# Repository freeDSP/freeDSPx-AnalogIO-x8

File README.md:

# AnalogIO-x8
Expansionboard with 8 analog balanced inputs and 8 analog balanced outputs for Infinitas and other freeDSPs

BOARD STATUS: Released!

MAIN COORDINATOR: [dspverden](https://github.com/dspverden)

IMPORTANT:

Please take care on which branch you're currently working!

Branches:

master - this branch always holds the latest released revision
develop - this is the develop branch with new features

## License
The plans for the AnalogIO-x8 board are published under a Creative Commons Attribution NonCommercial ShareAlike 4.0 International (CC BY-NC-SA 4.0) license, which allows the unrestricted use and modification of the module for non-commercial purposes. This means that experienced users can make their own version of the board, extending it and improving it, as long as they credit freeDSP and auverdion and release their designs under the same license.

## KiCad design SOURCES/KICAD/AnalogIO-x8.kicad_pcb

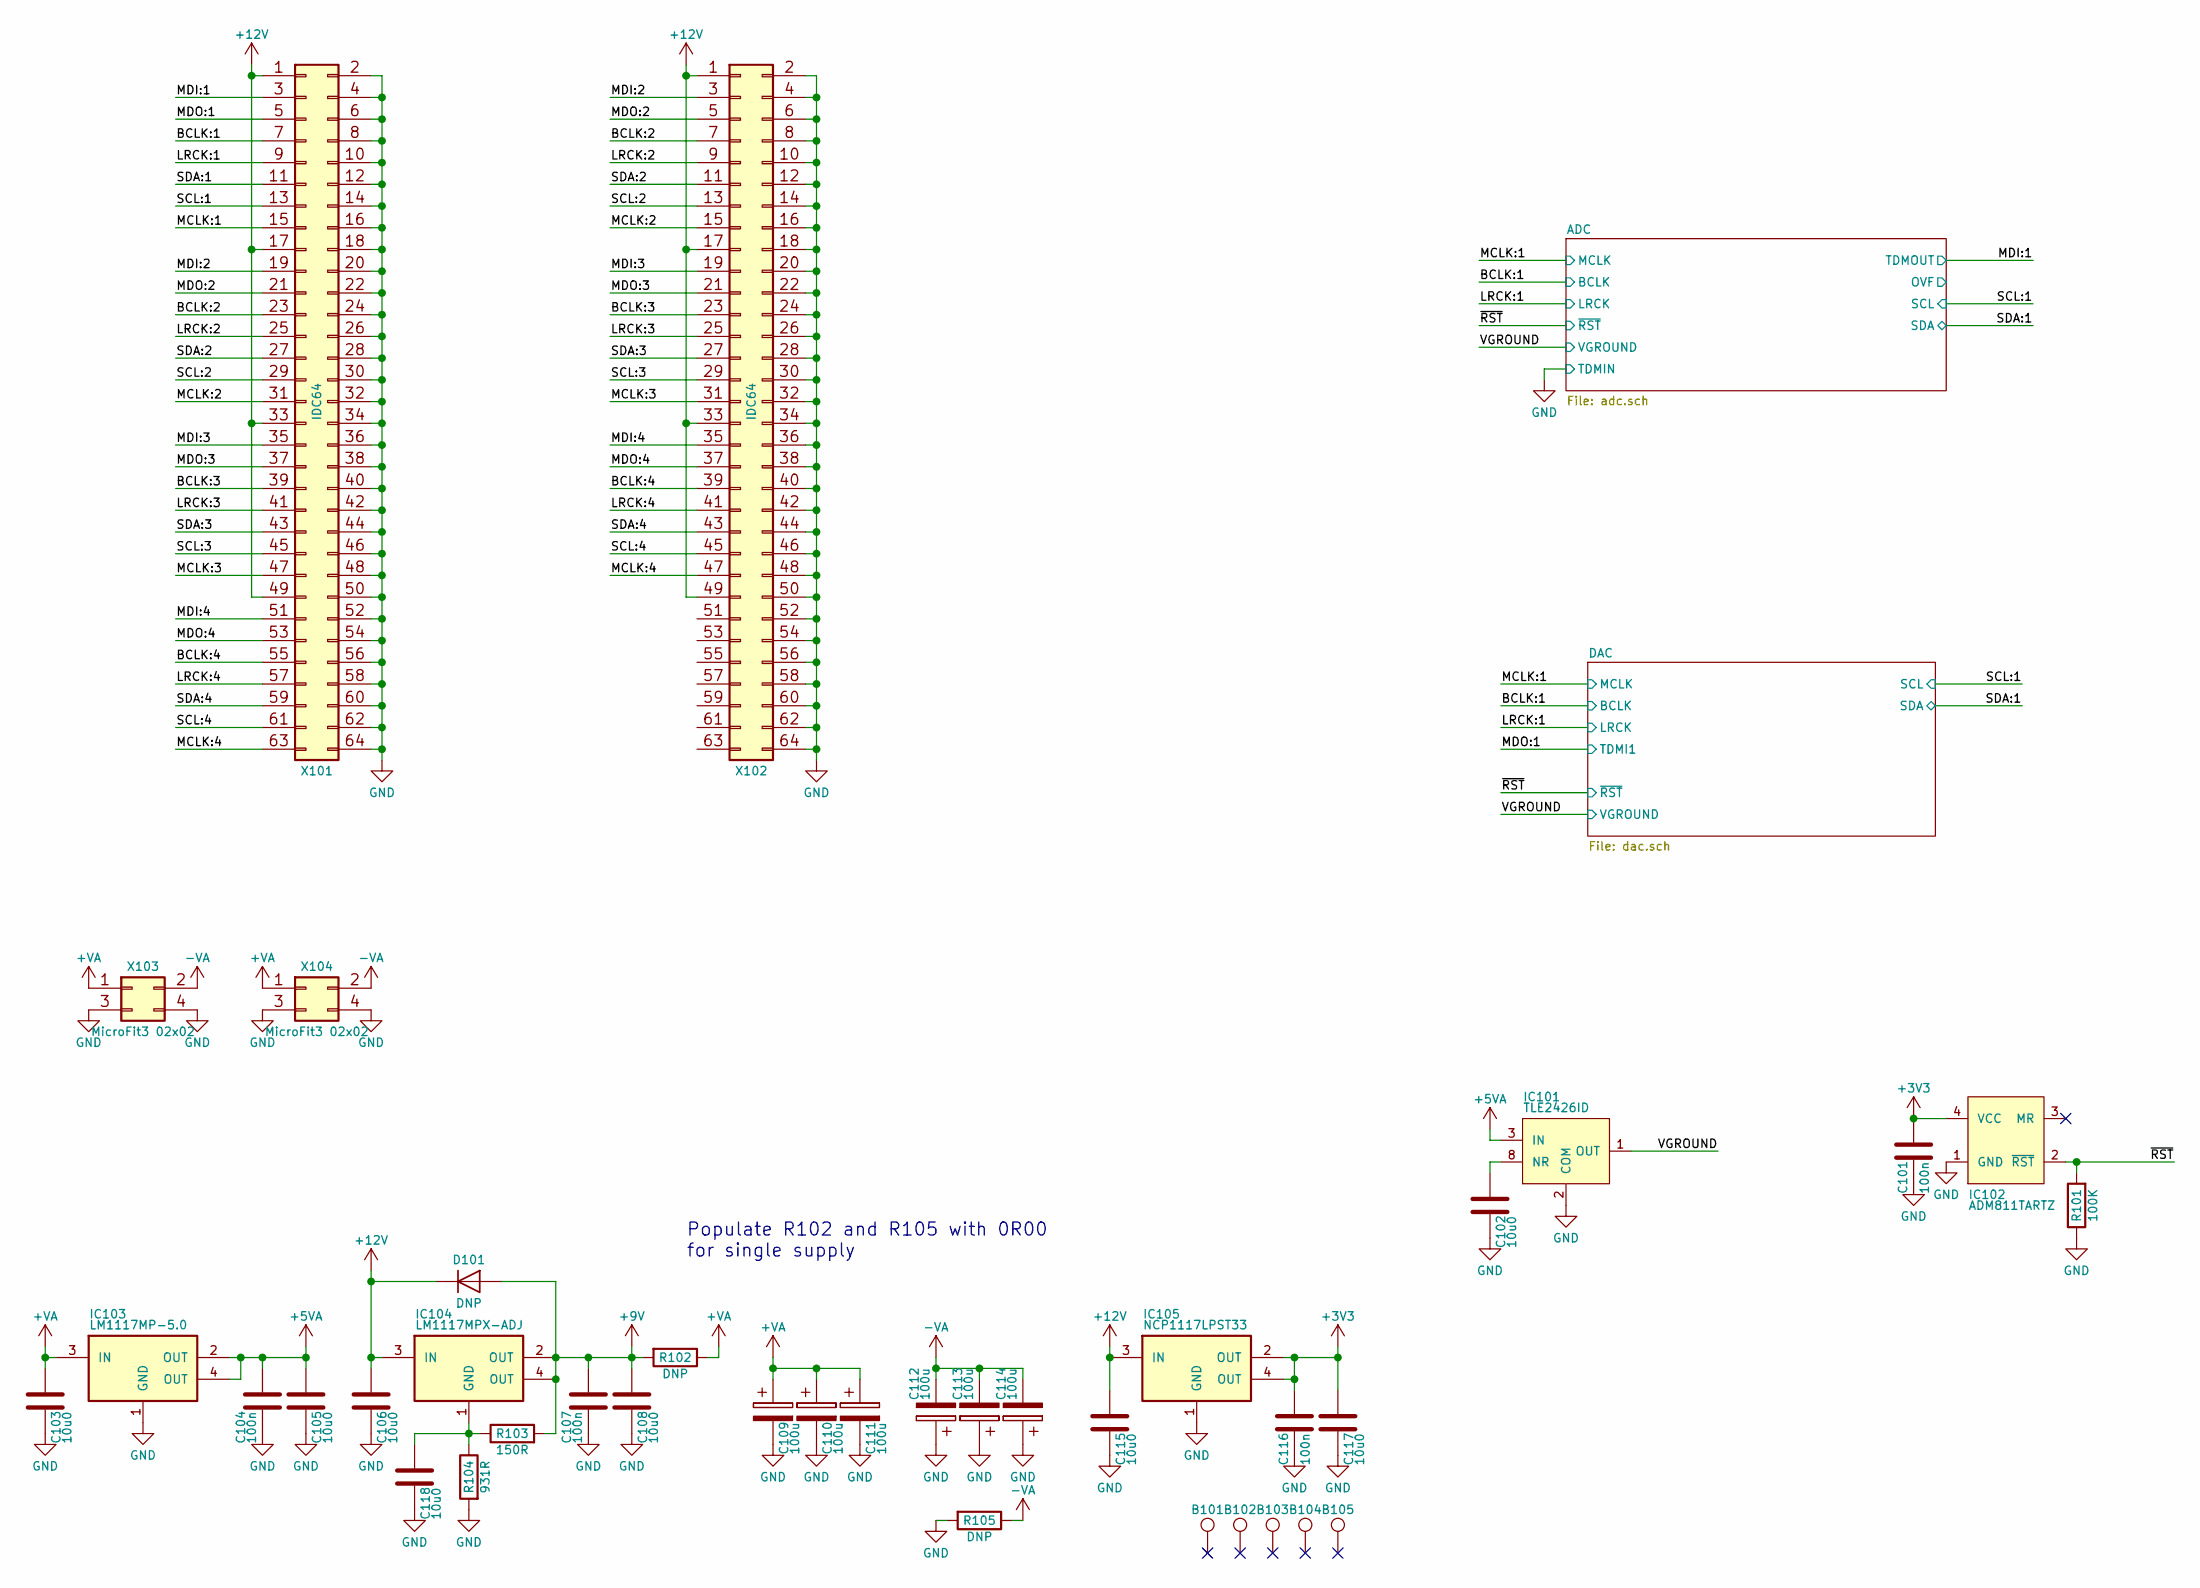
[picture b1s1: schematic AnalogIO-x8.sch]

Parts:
B101, B102, B103, B104, B105: TEST_1P; MountingHole_3.2mm_M3_DIN965_Pad
C101, C104, C107, C116: CAP_100n_50V_X7R_0805; C0805-X7R; digikey 399-1170-1-ND
C102, C103, C105, C106, C108, C115, C117, C118: CAP_10u0_25V_X5R_0805; C0805-X7R; digikey 490-10748-1-ND
C109, C110, C111, C112, C113, C114: CAP_100u_20%_25V_ALUM_RADIAL; C_Radial_D5_L11_P2; digikey 399-6102-ND
D101: DNP; MELF_Standard
IC101: IC_TLE2426ID; SOIC-8_3.9x4.9mm_Pitch1.27mm; digikey 296-1345-1-ND
IC102: IC_ADM811TARTZ; SOT-143; digikey ADM811TARTZ-REELCT-ND
IC103: IC_LM1117MP-5.0; SOT-223; digikey LM1117MP-5.0/NOPBCT-ND
IC104: IC_LM1117MPX-ADJ; SOT-223; digikey LM1117MPX-ADJ/NOPBCT-ND
IC105: IC_NCP1117LPST33; SOT-223; digikey NCP1117LPST33T3GOSCT-ND
R101: RES_100K_1%_0.125W_Thick_0805; C0805-RES; digikey 311-100KCRCT-ND
R102, R105: DNP; Resistor_Horizontal_RM7mm
R103: RES_150R_1%_0.25W_Thin_0805; C0805-RES; digikey RNCP0805FTD150RCT-ND
R104: RES_931R_1%_0.125W_Thick_0805; C0805-RES; digikey 311-931CRCT-ND
X101, X102: CON_IDC64; IDC64; digikey ED10532-ND
X103, X104: CON_MicroFit3_02x02; Microfit3_43045-0428; digikey WM10670-ND

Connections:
+3V3: C101.2, C116.2, C117.1, IC102.4 (VCC), IC105.2 (OUT), IC105.4 (OUT); also elsewhere on the board
+5VA: C104.2, C105.1, IC101.3 (IN), IC103.2 (OUT), IC103.4 (OUT); also elsewhere on the board
+9V: C107.2, C108.1, D101.2 (A), IC104.2 (OUT), IC104.4 (OUT), R102.2, R103.2
+12V: C106.1, C115.1, D101.1 (K), IC104.3 (IN), IC105.3 (IN), X101.1, X101.17, X101.33, X101.49, X102.1, X102.17, X102.33, X102.49
+VA: C103.1, C109.1, C110.1, C111.1, IC103.3 (IN), R102.1, X103.1, X104.1; also elsewhere on the board
-VA: C112.2, C113.2, C114.2, R105.1, X103.2, X104.2; also elsewhere on the board
/BCLK:1: X101.7; also elsewhere on the board
/BCLK:2: X101.23, X102.7
/BCLK:3: X101.39, X102.23
/BCLK:4: X101.55, X102.39
/LRCK:1: X101.9; also elsewhere on the board
/LRCK:2: X101.25, X102.9
/LRCK:3: X101.41, X102.25
/LRCK:4: X101.57, X102.41
/MCLK:1: X101.15; also elsewhere on the board
/MCLK:2: X101.31, X102.15
/MCLK:3: X101.47, X102.31
/MCLK:4: X101.63, X102.47
/MDI:1: X101.3; also elsewhere on the board
/MDI:2: X101.19, X102.3
/MDI:3: X101.35, X102.19
/MDI:4: X101.51, X102.35
/MDO:1: X101.5; also elsewhere on the board
/MDO:2: X101.21, X102.5
/MDO:3: X101.37, X102.21
/MDO:4: X101.53, X102.37
/SCL:1: X101.13; also elsewhere on the board
/SCL:2: X101.29, X102.13
/SCL:3: X101.45, X102.29
/SCL:4: X101.61, X102.45
/SDA:1: X101.11; also elsewhere on the board
/SDA:2: X101.27, X102.11
/SDA:3: X101.43, X102.27
/SDA:4: X101.59, X102.43
/VGROUND: IC101.1 (OUT); also elsewhere on the board
/~RST: IC102.2 (~RST), R101.2; also elsewhere on the board
GND: C101.1, C102.2, C103.2, C104.1, C105.2, C106.2, C107.1, C108.2, C109.2, C110.2, C111.2, C112.1, C113.1, C114.1, C115.2, C116.1, C117.2, C118.2, IC101.2 (COM), IC102.1 (GND), IC103.1 (GND), IC105.1 (GND), R101.1, R104.2, R105.2, X101.2, X101.4, X101.6, X101.8, X101.10, X101.12, X101.14, X101.16, X101.18, X101.20, X101.22, X101.24, X101.26, X101.28, X101.30, X101.32, X101.34, X101.36, X101.38, X101.40, X101.42, X101.44, X101.46, X101.48, X101.50, X101.52, X101.54, X101.56, X101.58, X101.60, X101.62, X101.64, X102.2, X102.4, X102.6, X102.8, X102.10, X102.12, X102.14, X102.16, X102.18, X102.20, X102.22, X102.24, X102.26, X102.28, X102.30, X102.32, X102.34, X102.36, X102.38, X102.40, X102.42, X102.44, X102.46, X102.48, X102.50, X102.52, X102.54, X102.56, X102.58, X102.60, X102.62, X102.64, X103.3, X103.4, X104.3, X104.4; also elsewhere on the board
unnamed: C102.1, IC101.8 (NR)
unnamed: C118.1, IC104.1 (GND), R103.1, R104.1

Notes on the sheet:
Populate R102 and R105 with 0R00 for single supply

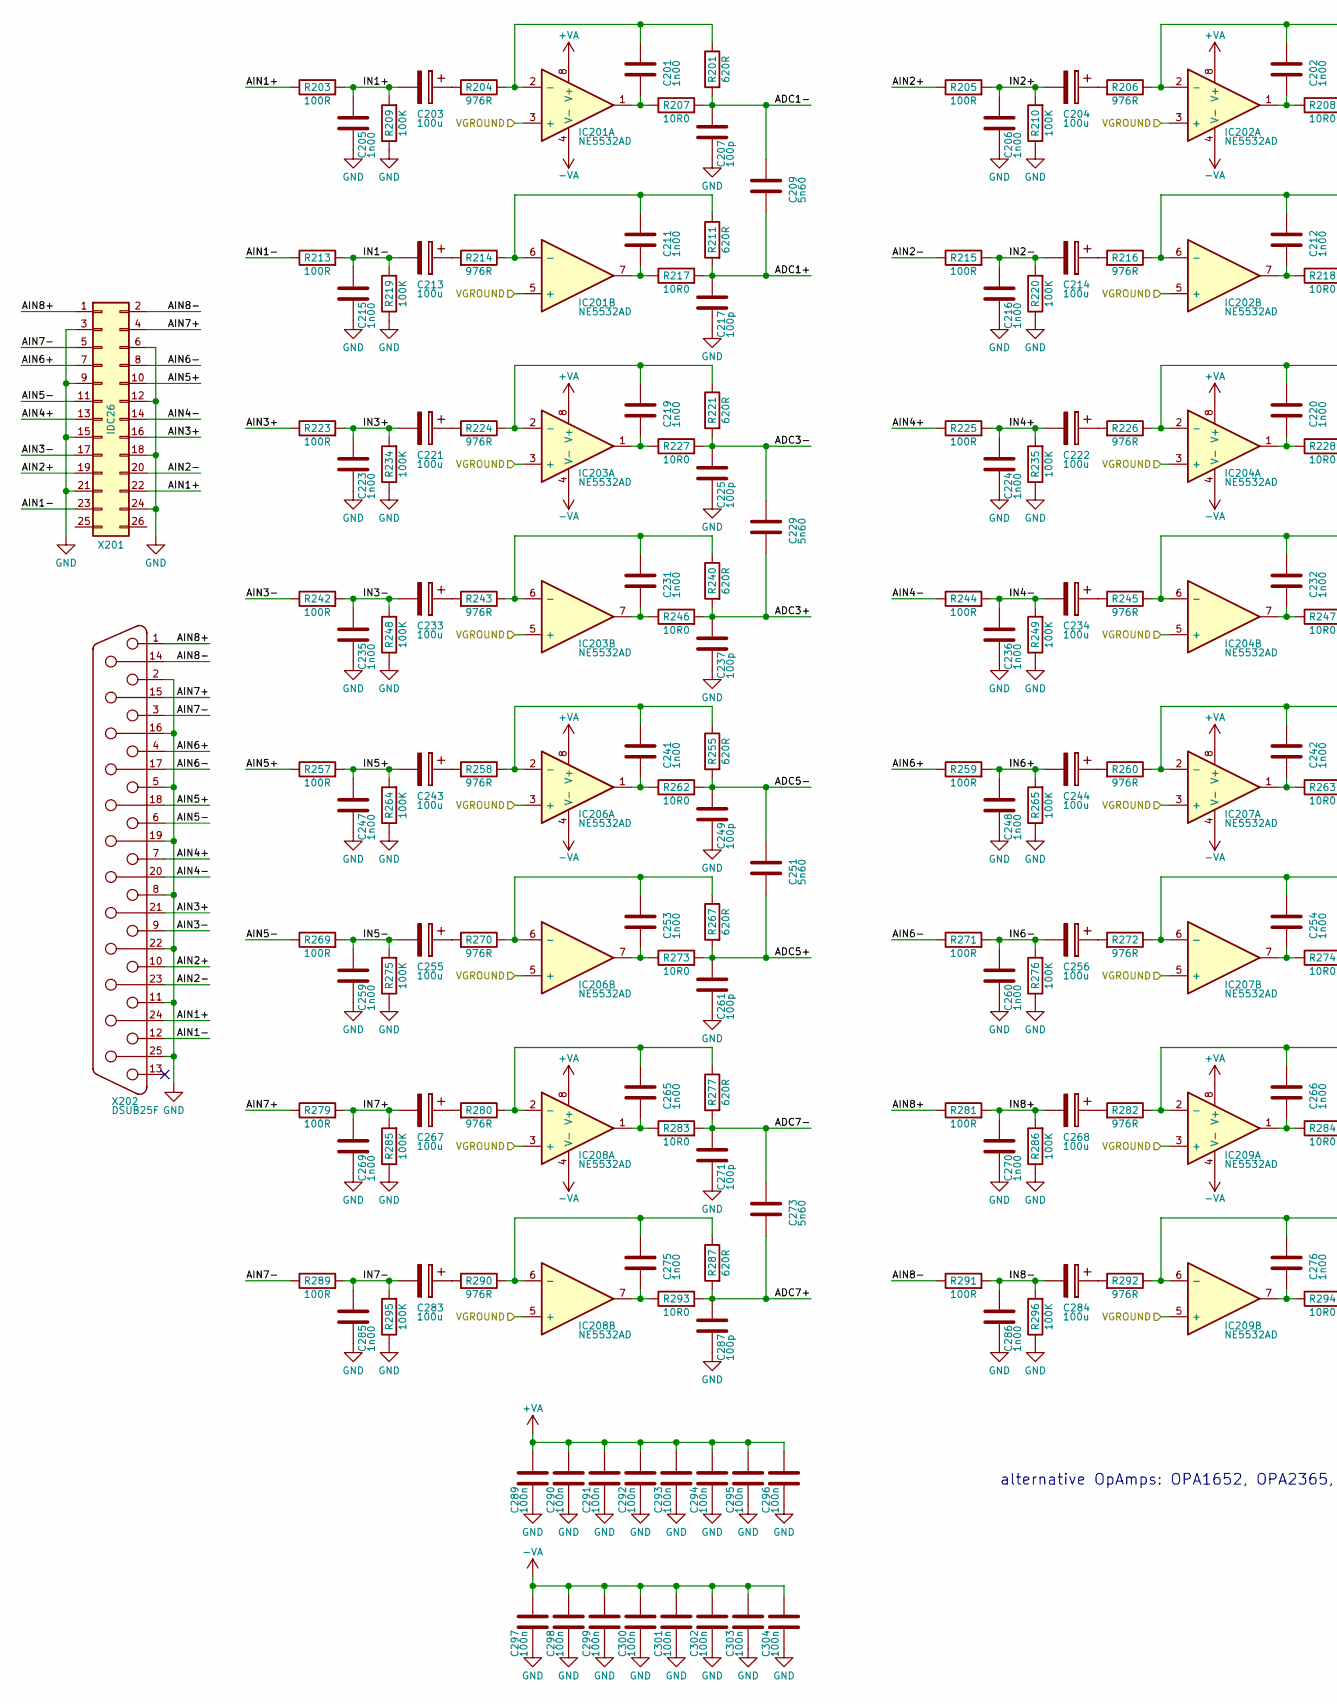
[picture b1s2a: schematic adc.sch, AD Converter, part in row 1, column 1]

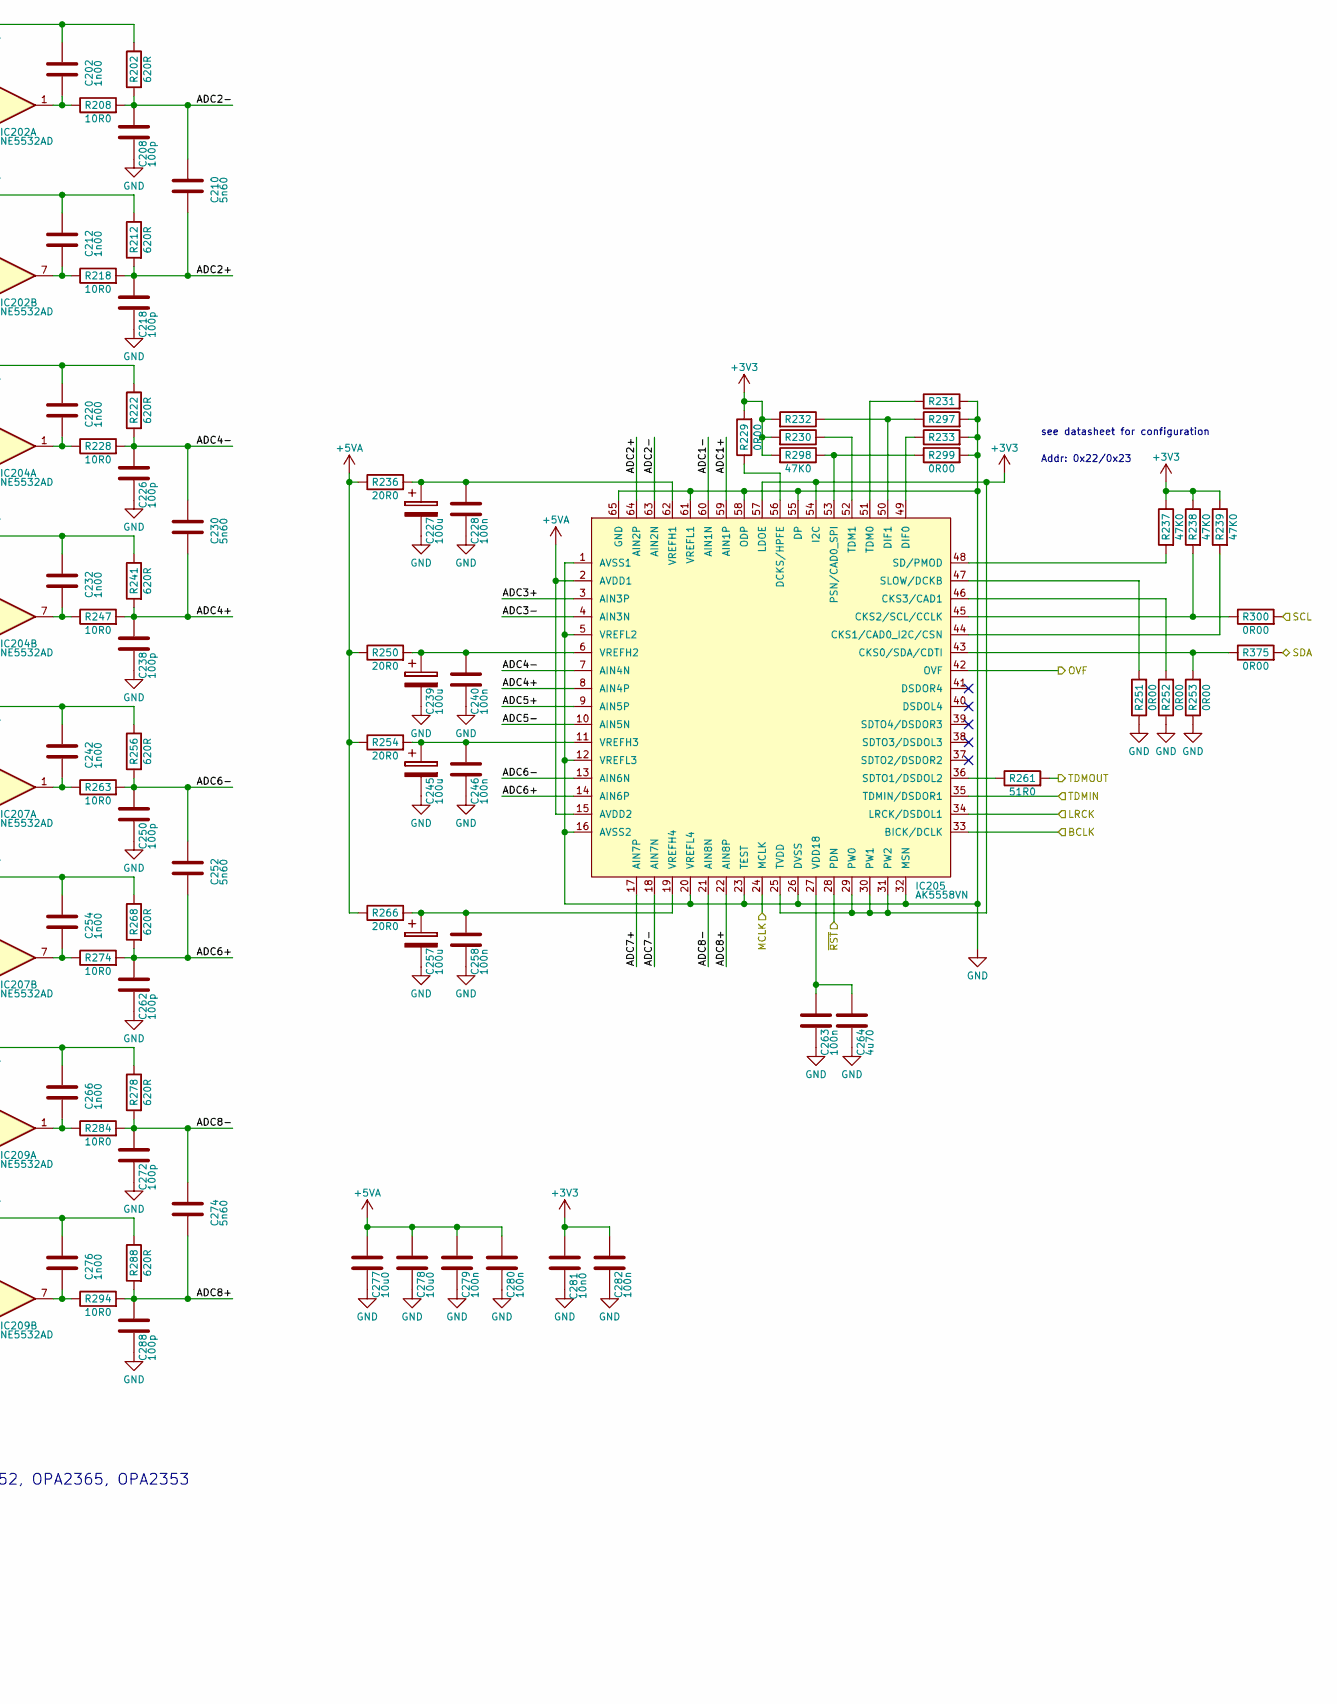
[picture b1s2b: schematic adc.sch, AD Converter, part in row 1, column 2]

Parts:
C201, C202, C211, C212, C219, C220, C231, C232, C241, C242, C253, C254, C265, C266, C275, C276: CAP_1n00_5%_50V_PPS_0805; C0805-X7R; digikey PCF1328CT-ND
C203, C204, C213, C214, C221, C222, C227, C233, C234, C239, C243, C244, C245, C255, C256, C257, C267, C268, C283, C284: CAP_100u_20%_25V_ALUM_RADIAL; C_Radial_D5_L11_P2; digikey 399-6102-ND
C205, C206, C215, C216, C223, C224, C235, C236, C247, C248, C259, C260, C269, C270, C285, C286: CAP_1n00_50V_X7R_0805; C0805-X7R; digikey 399-1147-1-ND
C207, C208, C217, C218, C225, C226, C237, C238, C249, C250, C261, C262, C271, C272, C287, C288: CAP_100p_50V_C0G/NP0_0805; C0805-X7R; digikey 399-1122-1-ND
C209, C210, C229, C230, C251, C252, C273, C274: CAP_5n60_5%_16V_PPS_0805; C0805-X7R; digikey PCF1193CT-ND
C228, C240, C246, C258, C263, C279, C280, C282, C289, C290, C291, C292, C293, C294, C295, C296, C297, C298, C299, C300, C301, C302, C303, C304: CAP_100n_50V_X7R_0805; C0805-X7R; digikey 399-1170-1-ND
C264: CAP_4u70_25V_X5R_0805; C0805-X7R; digikey 490-5422-1-ND
C277, C278: CAP_10u0_25V_X5R_0805; C0805-X7R; digikey 490-10748-1-ND
C281: CAP_10n0_50V_X7R_0805; C0805-X7R; digikey 311-1136-1-ND
IC201, IC202, IC203, IC204, IC206, IC207, IC208, IC209: IC_NE5532AD_SOIC8; SOIC8_3.9x4.9mm_Pitch1.27mm; digikey NE5532AD8R2GOSCT-ND
IC205: IC_AK5558VN; QFN64_9x9mm_Pitch0.5mm_EP_Handsoldering; digikey 974-1128-1-ND
R201, R202, R211, R212, R221, R222, R240, R241, R255, R256, R267, R268, R277, R278, R287, R288: RES_620R_0.5%_0.1W_Thin_0805; C0805-RES; digikey RR12P620DCT-ND
R203, R205, R213, R215, R223, R225, R242, R244, R257, R259, R269, R271, R279, R281, R289, R291: RES_100R_1%_0.25W_Thin_0805; C0805-RES; digikey RNCP0805FTD100RCT-ND
R204, R206, R214, R216, R224, R226, R243, R245, R258, R260, R270, R272, R280, R282, R290, R292: RES_976R_0.5%_0.1W_Thin_0805; C0805-RES; digikey 408-1761-1-ND
R207, R208, R217, R218, R227, R228, R246, R247, R262, R263, R273, R274, R283, R284, R293, R294: RES_10R0_1%_0.25W_Thin_0805; C0805-RES; digikey RNCP0805FTD10R0CT-ND
R209, R210, R219, R220, R234, R235, R248, R249, R264, R265, R275, R276, R285, R286, R295, R296: RES_100K_1%_0.125W_Thick_0805; C0805-RES; digikey 311-100KCRCT-ND
R229, R231, R233, R251, R252, R253, R297, R299, R300, R375: RES_0R00_1%_0.125W_Thick_0805; C0805-RES; digikey 311-0.0ARCT-ND
R230, R232, R237, R238, R239, R298: RES_47K0_1%_0.125W_Thick_0805; C0805-RES; digikey 311-47.0KCRCT-ND
R236, R250, R254, R266: RES_20R0_1%_0.125W_Thick_0805; C0805-RES; digikey 311-20.0CRCT-ND
R261: RES_51R0_1%_0.125W_Thick_0805; C0805-RES; digikey 311-51.0CRCT-ND
X201: CON_IDC26; IDC_Header_Straight_26pins; digikey 377-2269-ND
X202: CON_DSUB25F; DSUB25FC; digikey AE10937-ND

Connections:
+3V3: C281.1, C282.2, IC205.25 (TVDD), IC205.29 (PW0), IC205.30 (PW1), IC205.31 (PW2), IC205.54 (I2C), IC205.57 (LDOE), R229.2, R230.2, R232.2, R237.1, R238.1, R239.1, R298.2; also elsewhere on the board
+5VA: C277.1, C278.1, C279.2, C280.2, IC205.2 (AVDD1), IC205.15 (AVDD2), R236.1, R250.1, R254.1, R266.1; also elsewhere on the board
+VA: C289.2, C290.2, C291.2, C292.2, C293.2, C294.2, C295.2, C296.2, IC201.8 (V+), IC202.8 (V+), IC203.8 (V+), IC204.8 (V+), IC206.8 (V+), IC207.8 (V+), IC208.8 (V+), IC209.8 (V+); also elsewhere on the board
-VA: C297.2, C298.2, C299.2, C300.2, C301.2, C302.2, C303.2, C304.2, IC201.4 (V-), IC202.4 (V-), IC203.4 (V-), IC204.4 (V-), IC206.4 (V-), IC207.4 (V-), IC208.4 (V-), IC209.4 (V-); also elsewhere on the board
/ADC-1/ADC1+: C209.2, C217.2, IC205.59 (AIN1P), R211.2, R217.2
/ADC-1/ADC1-: C207.2, C209.1, IC205.60 (AIN1N), R201.2, R207.2
/ADC-1/ADC2+: C210.2, C218.2, IC205.64 (AIN2P), R212.2, R218.2
/ADC-1/ADC2-: C208.2, C210.1, IC205.63 (AIN2N), R202.2, R208.2
/ADC-1/ADC3+: C229.2, C237.2, IC205.3 (AIN3P), R240.2, R246.2
/ADC-1/ADC3-: C225.2, C229.1, IC205.4 (AIN3N), R221.2, R227.2
/ADC-1/ADC4+: C230.2, C238.2, IC205.8 (AIN4P), R241.2, R247.2
/ADC-1/ADC4-: C226.2, C230.1, IC205.7 (AIN4N), R222.2, R228.2
/ADC-1/ADC5+: C251.2, C261.2, IC205.9 (AIN5P), R267.2, R273.2
/ADC-1/ADC5-: C249.2, C251.1, IC205.10 (AIN5N), R255.2, R262.2
/ADC-1/ADC6+: C252.2, C262.2, IC205.14 (AIN6P), R268.2, R274.2
/ADC-1/ADC6-: C250.2, C252.1, IC205.13 (AIN6N), R256.2, R263.2
/ADC-1/ADC7+: C273.2, C287.2, IC205.17 (AIN7P), R287.2, R293.2
/ADC-1/ADC7-: C271.2, C273.1, IC205.18 (AIN7N), R277.2, R283.2
/ADC-1/ADC8+: C274.2, C288.2, IC205.22 (AIN8P), R288.2, R294.2
/ADC-1/ADC8-: C272.2, C274.1, IC205.21 (AIN8N), R278.2, R284.2
/ADC-1/AIN1+: R203.1, X201.22, X202.24
/ADC-1/AIN1-: R213.1, X201.23, X202.12
/ADC-1/AIN2+: R205.1, X201.19, X202.10
/ADC-1/AIN2-: R215.1, X201.20, X202.23
/ADC-1/AIN3+: R223.1, X201.16, X202.21
/ADC-1/AIN3-: R242.1, X201.17, X202.9
/ADC-1/AIN4+: R225.1, X201.13, X202.7
/ADC-1/AIN4-: R244.1, X201.14, X202.20
/ADC-1/AIN5+: R257.1, X201.10, X202.18
/ADC-1/AIN5-: R269.1, X201.11, X202.6
/ADC-1/AIN6+: R259.1, X201.7, X202.4
/ADC-1/AIN6-: R271.1, X201.8, X202.17
/ADC-1/AIN7+: R279.1, X201.4, X202.15
/ADC-1/AIN7-: R289.1, X201.5, X202.3
/ADC-1/AIN8+: R281.1, X201.1, X202.1
/ADC-1/AIN8-: R291.1, X201.2, X202.14
/ADC-1/IN1+: C203.2, C205.1, R203.2, R209.2
/ADC-1/IN1-: C213.2, C215.1, R213.2, R219.2
/ADC-1/IN2+: C204.2, C206.1, R205.2, R210.2
/ADC-1/IN2-: C214.2, C216.1, R215.2, R220.2
/ADC-1/IN3+: C221.2, C223.1, R223.2, R234.2
/ADC-1/IN3-: C233.2, C235.1, R242.2, R248.2
/ADC-1/IN4+: C222.2, C224.1, R225.2, R235.2
/ADC-1/IN4-: C234.2, C236.1, R244.2, R249.2
/ADC-1/IN5+: C243.2, C247.1, R257.2, R264.2
/ADC-1/IN5-: C255.2, C259.1, R269.2, R275.2
/ADC-1/IN6+: C244.2, C248.1, R259.2, R265.2
/ADC-1/IN6-: C256.2, C260.1, R271.2, R276.2
/ADC-1/IN7+: C267.2, C269.1, R279.2, R285.2
/ADC-1/IN7-: C283.2, C285.1, R289.2, R295.2
/ADC-1/IN8+: C268.2, C270.1, R281.2, R286.2
/ADC-1/IN8-: C284.2, C286.1, R291.2, R296.2
/BCLK:1: IC205.33 (BICK/DCLK); also elsewhere on the board
/LRCK:1: IC205.34 (LRCK/DSDOL1); also elsewhere on the board
/MCLK:1: IC205.24 (MCLK); also elsewhere on the board
/MDI:1: R261.2; also elsewhere on the board
/SCL:1: R300.2; also elsewhere on the board
/SDA:1: R375.2; also elsewhere on the board
/VGROUND: IC201.3 (+), IC201.5 (+), IC202.3 (+), IC202.5 (+), IC203.3 (+), IC203.5 (+), IC204.3 (+), IC204.5 (+), IC206.3 (+), IC206.5 (+), IC207.3 (+), IC207.5 (+), IC208.3 (+), IC208.5 (+), IC209.3 (+), IC209.5 (+); also elsewhere on the board
/~RST: IC205.28 (PDN); also elsewhere on the board
GND: C205.2, C206.2, C207.1, C208.1, C215.2, C216.2, C217.1, C218.1, C223.2, C224.2, C225.1, C226.1, C227.2, C228.1, C235.2, C236.2, C237.1, C238.1, C239.2, C240.1, C245.2, C246.1, C247.2, C248.2, C249.1, C250.1, C257.2, C258.1, C259.2, C260.2, C261.1, C262.1, C263.1, C264.2, C269.2, C270.2, C271.1, C272.1, C277.2, C278.2, C279.1, C280.1, C281.2, C282.1, C285.2, C286.2, C287.1, C288.1, C289.1, C290.1, C291.1, C292.1, C293.1, C294.1, C295.1, C296.1, C297.1, C298.1, C299.1, C300.1, C301.1, C302.1, C303.1, C304.1, IC205.1 (AVSS1), IC205.5 (VREFL2), IC205.12 (VREFL3), IC205.16 (AVSS2), IC205.20 (VREFL4), IC205.23 (TEST), IC205.26 (DVSS), IC205.32 (MSN), IC205.35 (TDMIN/DSDOR1), IC205.55 (DP), IC205.58 (ODP), IC205.61 (VREFL1), IC205.65 (GND), R209.1, R210.1, R219.1, R220.1, R231.2, R233.2, R234.1, R235.1, R248.1, R249.1, R251.1, R252.1, R253.1, R264.1, R265.1, R275.1, R276.1, R285.1, R286.1, R295.1, R296.1, R297.2, R299.2, X201.3, X201.6, X201.9, X201.12, X201.15, X201.18, X201.21, X201.24, X202.2, X202.5, X202.8, X202.11, X202.16, X202.19, X202.22, X202.25; also elsewhere on the board
unnamed: C201.1, IC201.2 (-), R201.1, R204.1
unnamed: C201.2, IC201.1, R207.1
unnamed: C202.1, IC202.2 (-), R202.1, R206.1
unnamed: C202.2, IC202.1, R208.1
unnamed: C203.1, R204.2
unnamed: C204.1, R206.2
unnamed: C211.1, IC201.6 (-), R211.1, R214.1
unnamed: C211.2, IC201.7, R217.1
unnamed: C212.1, IC202.6 (-), R212.1, R216.1
unnamed: C212.2, IC202.7, R218.1
unnamed: C213.1, R214.2
unnamed: C214.1, R216.2
unnamed: C219.1, IC203.2 (-), R221.1, R224.1
unnamed: C219.2, IC203.1, R227.1
unnamed: C220.1, IC204.2 (-), R222.1, R226.1
unnamed: C220.2, IC204.1, R228.1
unnamed: C221.1, R224.2
unnamed: C222.1, R226.2
unnamed: C227.1, C228.2, IC205.62 (VREFH1), R236.2
unnamed: C231.1, IC203.6 (-), R240.1, R243.1
unnamed: C231.2, IC203.7, R246.1
unnamed: C232.1, IC204.6 (-), R241.1, R245.1
unnamed: C232.2, IC204.7, R247.1
unnamed: C233.1, R243.2
unnamed: C234.1, R245.2
unnamed: C239.1, C240.2, IC205.6 (VREFH2), R250.2
unnamed: C241.1, IC206.2 (-), R255.1, R258.1
unnamed: C241.2, IC206.1, R262.1
unnamed: C242.1, IC207.2 (-), R256.1, R260.1
unnamed: C242.2, IC207.1, R263.1
unnamed: C243.1, R258.2
unnamed: C244.1, R260.2
unnamed: C245.1, C246.2, IC205.11 (VREFH3), R254.2
unnamed: C253.1, IC206.6 (-), R267.1, R270.1
unnamed: C253.2, IC206.7, R273.1
unnamed: C254.1, IC207.6 (-), R268.1, R272.1
unnamed: C254.2, IC207.7, R274.1
unnamed: C255.1, R270.2
unnamed: C256.1, R272.2
unnamed: C257.1, C258.2, IC205.19 (VREFH4), R266.2
unnamed: C263.2, C264.1, IC205.27 (VDD18)
unnamed: C265.1, IC208.2 (-), R277.1, R280.1
unnamed: C265.2, IC208.1, R283.1
unnamed: C266.1, IC209.2 (-), R278.1, R282.1
unnamed: C266.2, IC209.1, R284.1
unnamed: C267.1, R280.2
unnamed: C268.1, R282.2
unnamed: C275.1, IC208.6 (-), R287.1, R290.1
unnamed: C275.2, IC208.7, R293.1
unnamed: C276.1, IC209.6 (-), R288.1, R292.1
unnamed: C276.2, IC209.7, R294.1
unnamed: C283.1, R290.2
unnamed: C284.1, R292.2
unnamed: IC205.36 (SDTO1/DSDOL2), R261.1
unnamed: IC205.43 (CKS0/SDA/CDTI), R253.2, R375.1
unnamed: IC205.44 (CKS1/CAD0_I2C/CSN), R239.2
unnamed: IC205.45 (CKS2/SCL/CCLK), R238.2, R300.1
unnamed: IC205.46 (CKS3/CAD1), R252.2
unnamed: IC205.47 (SLOW/DCKB), R251.2
unnamed: IC205.48 (SD/PMOD), R237.2
unnamed: IC205.49 (DIF0), R233.1
unnamed: IC205.50 (DIF1), R232.1, R297.1
unnamed: IC205.51 (TDM0), R231.1
unnamed: IC205.52 (TDM1), R230.1
unnamed: IC205.53 (PSN/CAD0_SPI), R298.1, R299.1
unnamed: IC205.56 (DCKS/HPFE), R229.1

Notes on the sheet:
see datasheet for configuration
alternative OpAmps: OPA1652, OPA2365, OPA2353
Addr: 0x22/0x23

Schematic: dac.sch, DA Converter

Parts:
C305, C306, C313, C314, C318, C319, C325, C328, C329, C333, C334, C335, C344, C345, C349, C350, C351, C357, C360, C361: CAP_100u_20%_25V_ALUM_RADIAL; C_Radial_D5_L11_P2; digikey 399-6102-ND
C307, C308, C315, C316, C320, C321, C330, C331, C336, C337, C346, C347, C352, C353, C362, C363: CAP_470p_2%_50V_PPS_0805; C0805-X7R; digikey PCF1292CT-ND
C309, C310, C322, C323, C338, C339, C354, C355: CAP_27p0_50V_C0G/NP0_0805; C0805-X7R; digikey 399-1114-1-ND
C311, C312, C326, C327, C342, C343, C358, C359: CAP_3n90_5%_16V_PPS_0805; C0805-X7R; digikey PCF1191CT-ND
C317: CAP_1u00_16V_X7R_0805; C0805-X7R; digikey 311-1365-1-ND
C324, C332, C340, C348, C356, C365, C366, C367, C368, C369, C370, C371, C372, C373, C374, C375, C376, C377, C378, C379, C380, C381: CAP_100n_50V_X7R_0805; C0805-X7R; digikey 399-1170-1-ND
C341, C364: CAP_10u0_25V_X5R_0805; C0805-X7R; digikey 490-10748-1-ND
IC301, IC302, IC303, IC304, IC306, IC307, IC308, IC309: IC_NE5532AD_SOIC8; SOIC8_3.9x4.9mm_Pitch1.27mm; digikey NE5532AD8R2GOSCT-ND
IC305: IC_AK4458VN; QFN48_7x7mm_Pitch0.5mm_EP_Handsoldering; digikey 974-1082-1-ND
R301, R303, R311, R313, R317, R319, R328, R330, R335, R337, R345, R347, R352, R354, R368, R370: RES_4K42_0.5%_0.1W_Thin_0805; C0805-RES; digikey RR12P4.42KDCT-ND
R302, R304, R315, R316, R318, R320, R332, R333, R336, R338, R350, R351, R353, R355, R372, R373: RES_3K40_0.5%_0.1W_Thin_0805; C0805-RES; digikey RR12P3.4KDCT-ND
R305, R306, R312, R314, R321, R322, R329, R331, R339, R340, R346, R348, R357, R358, R369, R371: RES_150R_1%_0.25W_Thin_0805; C0805-RES; digikey RNCP0805FTD150RCT-ND
R307, R308, R309, R310, R324, R325, R326, R327, R341, R342, R343, R344, R362, R363, R366, R367: RES_4K70_1%_0.125W_Thin_0805; C0805-RES; digikey YAG3364CT-ND
R323, R334, R349, R356: RES_20R0_1%_0.125W_Thick_0805; C0805-RES; digikey 311-20.0CRCT-ND
R359, R360, R361, R364, R365, R376, R377: RES_0R00_1%_0.125W_Thick_0805; C0805-RES; digikey 311-0.0ARCT-ND
R374: RES_47K0_1%_0.125W_Thick_0805; C0805-RES; digikey 311-47.0KCRCT-ND
X301: CON_DSUB25F; DSUB25FC; digikey AE10937-ND
X302: CON_IDC26; IDC_Header_Straight_26pins; digikey 377-2269-ND

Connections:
+3V3: C364.1, C365.2, IC305.44 (LDOE), IC305.45 (TVDD), R361.1, R365.1, R374.2; also elsewhere on the board
+5VA: C340.2, C341.1, IC305.31 (AVDD), R323.2, R334.2, R349.2, R356.2; also elsewhere on the board
+VA: C366.2, C367.2, C368.2, C369.2, C370.2, C371.2, C372.2, C373.2, IC301.8 (V+), IC302.8 (V+), IC303.8 (V+), IC304.8 (V+), IC306.8 (V+), IC307.8 (V+), IC308.8 (V+), IC309.8 (V+); also elsewhere on the board
-VA: C374.2, C375.2, C376.2, C377.2, C378.2, C379.2, C380.2, C381.2, IC301.4 (V-), IC302.4 (V-), IC303.4 (V-), IC304.4 (V-), IC306.4 (V-), IC307.4 (V-), IC308.4 (V-), IC309.4 (V-); also elsewhere on the board
/BCLK:1: IC305.2 (BICK/DCLK); also elsewhere on the board
/DAC-1/AOUT1+: C305.2, X301.24, X302.22
/DAC-1/AOUT1-: C313.2, X301.12, X302.23
/DAC-1/AOUT2+: C306.2, X301.10, X302.19
/DAC-1/AOUT2-: C314.2, X301.23, X302.20
/DAC-1/AOUT3+: C318.2, X301.21, X302.16
/DAC-1/AOUT3-: C328.2, X301.9, X302.17
/DAC-1/AOUT4+: C319.2, X301.7, X302.13
/DAC-1/AOUT4-: C329.2, X301.20, X302.14
/DAC-1/AOUT5+: C334.2, X301.18, X302.10
/DAC-1/AOUT5-: C344.2, X301.6, X302.11
/DAC-1/AOUT6+: C335.2, X301.4, X302.7
/DAC-1/AOUT6-: C345.2, X301.17, X302.8
/DAC-1/AOUT7+: C350.2, X301.15, X302.4
/DAC-1/AOUT7-: C360.2, X301.3, X302.5
/DAC-1/AOUT8+: C351.2, X301.1, X302.1
/DAC-1/AOUT8-: C361.2, X301.14, X302.2
/DAC-1/DAC1+: IC305.18 (AOUTL1P), R311.2
/DAC-1/DAC1-: IC305.19 (AOUTL1N), R301.2
/DAC-1/DAC2+: IC305.23 (AOUTR1P), R313.2
/DAC-1/DAC2-: IC305.22 (AOUTR1N), R303.2
/DAC-1/DAC3+: IC305.24 (AOUTL2P), R328.2
/DAC-1/DAC3-: IC305.25 (AOUTL2N), R317.2
/DAC-1/DAC4+: IC305.29 (AOUTR2), R330.2
/DAC-1/DAC4-: IC305.28 (AOUTR2N), R319.2
/DAC-1/DAC5+: IC305.32 (AOUTL3P), R345.2
/DAC-1/DAC5-: IC305.33 (AOUTL3N), R335.2
/DAC-1/DAC6+: IC305.37 (AOUTR3P), R347.2
/DAC-1/DAC6-: IC305.36 (AOUTR3N), R337.2
/DAC-1/DAC7+: IC305.38 (AOUTL4P), R368.2
/DAC-1/DAC7-: IC305.39 (AOUTL4N), R352.2
/DAC-1/DAC8+: IC305.43 (AOUTR4P), R370.2
/DAC-1/DAC8-: IC305.42 (AOUTR4N), R354.2
/LRCK:1: IC305.3 (LRCK/DSDL1); also elsewhere on the board
/MCLK:1: IC305.1 (MCLK); also elsewhere on the board
/MDO:1: IC305.4 (SDTI1/DSDR1); also elsewhere on the board
/SCL:1: R376.1; also elsewhere on the board
/SDA:1: R377.1; also elsewhere on the board
/VGROUND: C315.2, C316.2, C330.2, C331.2, C346.2, C347.2, C362.2, C363.2, IC301.5 (+), IC302.5 (+), IC303.5 (+), IC304.5 (+), IC306.5 (+), IC307.5 (+), IC308.5 (+), IC309.5 (+), R315.2, R316.2, R332.2, R333.2, R350.2, R351.2, R372.2, R373.2; also elsewhere on the board
/~RST: IC305.48 (PDN); also elsewhere on the board
GND: C317.2, C324.1, C325.2, C332.1, C333.2, C340.1, C341.2, C348.1, C349.2, C356.1, C357.2, C364.2, C365.1, C366.1, C367.1, C368.1, C369.1, C370.1, C371.1, C372.1, C373.1, C374.1, C375.1, C376.1, C377.1, C378.1, C379.1, C380.1, C381.1, IC305.5 (SDTI2/DSDL2), IC305.6 (SDTI3/DSDR2/TDMO1), IC305.7 (SDTI4/DSDL3/TDMO2), IC305.8 (DSDR3), IC305.9 (DSDL4), IC305.10 (DSDR4), IC305.11 (DZF_/SMUTE), IC305.12 (CAD1/DCHAIN), IC305.20 (VREFL1), IC305.26 (VREFL2), IC305.30 (AVSS), IC305.35 (VREFL3), IC305.41 (VREFL4), IC305.46 (DVSS), IC305.49 (GND), R359.1, R360.1, R364.1, X301.2, X301.5, X301.8, X301.11, X301.16, X301.19, X301.22, X301.25, X302.3, X302.6, X302.9, X302.12, X302.15, X302.18, X302.21, X302.24; also elsewhere on the board
unnamed: C305.1, C307.1, IC301.1, R302.1, R309.2
unnamed: C306.1, C308.1, IC302.1, R304.1, R310.2
unnamed: C307.2, IC301.2 (-), R305.2
unnamed: C308.2, IC302.2 (-), R306.2
unnamed: C309.1, IC301.6 (-), R307.2, R309.1
unnamed: C309.2, C313.1, IC301.7, R307.1
unnamed: C310.1, IC302.6 (-), R308.2, R310.1
unnamed: C310.2, C314.1, IC302.7, R308.1
unnamed: C311.1, R301.1, R302.2, R305.1
unnamed: C311.2, R311.1, R312.1, R315.1
unnamed: C312.1, R303.1, R304.2, R306.1
unnamed: C312.2, R313.1, R314.1, R316.1
unnamed: C315.1, IC301.3 (+), R312.2
unnamed: C316.1, IC302.3 (+), R314.2
unnamed: C317.1, IC305.47 (VDD18)
unnamed: C318.1, C320.1, IC303.1, R318.1, R326.2
unnamed: C319.1, C321.1, IC304.1, R320.1, R327.2
unnamed: C320.2, IC303.2 (-), R321.2
unnamed: C321.2, IC304.2 (-), R322.2
unnamed: C322.1, IC303.6 (-), R324.2, R326.1
unnamed: C322.2, C328.1, IC303.7, R324.1
unnamed: C323.1, IC304.6 (-), R325.2, R327.1
unnamed: C323.2, C329.1, IC304.7, R325.1
unnamed: C324.2, C325.1, IC305.40 (VREFH4), R323.1
unnamed: C326.1, R317.1, R318.2, R321.1
unnamed: C326.2, R328.1, R329.1, R332.1
unnamed: C327.1, R319.1, R320.2, R322.1
unnamed: C327.2, R330.1, R331.1, R333.1
unnamed: C330.1, IC303.3 (+), R329.2
unnamed: C331.1, IC304.3 (+), R331.2
unnamed: C332.2, C333.1, IC305.34 (VREFH3), R334.1
unnamed: C334.1, C336.1, IC306.1, R336.1, R343.2
unnamed: C335.1, C337.1, IC307.1, R338.1, R344.2
unnamed: C336.2, IC306.2 (-), R339.2
unnamed: C337.2, IC307.2 (-), R340.2
unnamed: C338.1, IC306.6 (-), R341.2, R343.1
unnamed: C338.2, C344.1, IC306.7, R341.1
unnamed: C339.1, IC307.6 (-), R342.2, R344.1
unnamed: C339.2, C345.1, IC307.7, R342.1
unnamed: C342.1, R335.1, R336.2, R339.1
unnamed: C342.2, R345.1, R346.1, R350.1
unnamed: C343.1, R337.1, R338.2, R340.1
unnamed: C343.2, R347.1, R348.1, R351.1
unnamed: C346.1, IC306.3 (+), R346.2
unnamed: C347.1, IC307.3 (+), R348.2
unnamed: C348.2, C349.1, IC305.27 (VREFH2), R349.1
unnamed: C350.1, C352.1, IC308.1, R353.1, R366.2
unnamed: C351.1, C353.1, IC309.1, R355.1, R367.2
unnamed: C352.2, IC308.2 (-), R357.2
unnamed: C353.2, IC309.2 (-), R358.2
unnamed: C354.1, IC308.6 (-), R362.2, R366.1
unnamed: C354.2, C360.1, IC308.7, R362.1
unnamed: C355.1, IC309.6 (-), R363.2, R367.1
unnamed: C355.2, C361.1, IC309.7, R363.1
unnamed: C356.2, C357.1, IC305.21 (VREFH1), R356.1
unnamed: C358.1, R352.1, R353.2, R357.1
unnamed: C358.2, R368.1, R369.1, R372.1
unnamed: C359.1, R354.1, R355.2, R358.1
unnamed: C359.2, R370.1, R371.1, R373.1
unnamed: C362.1, IC308.3 (+), R369.2
unnamed: C363.1, IC309.3 (+), R371.2
unnamed: IC305.13 (SDA/CDTI/TDM0), R364.2, R377.2
unnamed: IC305.14 (SCL/CCLK/TDM1), R365.2, R376.2
unnamed: IC305.15 (CAD0_I2C/CSN/_DIF), R359.2
unnamed: IC305.16 (PS/CAD0_SPI), R360.2, R374.1
unnamed: IC305.17 (I2C), R361.2

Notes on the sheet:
I2C Addr: 0x20/0x21
For Infinitas R359, R360, R376, R377: 0R00 R364, R365, R374: DNP See datasheet for other configurations. Remove R376 and R377 for hardware mode (parallel mode).
